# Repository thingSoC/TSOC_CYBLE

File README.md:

# TSOC_CYBLE

A thingSoC Adapter board for the Cypress Semiconductor CYBLE022-001 BLTE Radio Module.

[TSOC_CYBLE](https://github.com/thingSoC/TSOC_CYBLE)

The thingSoC "Grovey Series" was designed as "Everyday Electronics", a no-frills, low cost, approach to modular embedded product design.
thingSoC boards are similar in size to most break-out-boards (BOBs), but feature a standardized stacking pinout, as well as an I2C metadata store (EEPROM)
to indicate what peripherals are installed.

---------------------------------------

## TSOC_CYBLE Application Pictures

[*TSOC_CYBLE*](https://github.com/thingSoC/TSOC_CYBLE)

---------------------------------------

## TSOC_CYBLE Arduino Sketch Examples

Under the "examples" directory are several Arduino IDE examples for using the TSOC_CYBLE board with Arduino IDE.
Using the Arduino "Wire" library for I2C communications, it is simple to control the TSOC_CYBLE

```c

 coming soon...

```

---------------------------------------
## TSOC_CYBLE Programming

You can reprogram the board using any USB to UART adapter :

In order to reprogram the Cypress PSoC4 device, you will need to download and install the PSoC Creator tool, which includes a serial bootloader host application.

Select Tools -> Bootloader Host 

Then select the hex (cyacd) file that you wish to program, and the COM: port of your device. Proess the "Upload" button to reflash the device.

[PSoC Creator Bootloader Host](https://github.com/thingSoC/TSOC_CYBLE)

---------------------------------------
## Other Applications

The TSOC_CYBLE can also drive other devices, such as Servos, Motors, Relays and more.

---------------------------------------

## TSOC_CYBLE Status <a name="TSOC_CYBLE_status"/>

**09/02/2016:** 
Revision 1.0 - Initial Layout 

---------------------------------------
## TSOC_CYBLE Model Images

[TSOC_CYBLE](https://github.com/thingSoC/TSOC_CYBLE)

[TSOC_CYBLE](https://github.com/thingSoC/TSOC_CYBLE)

---------------------------------------

## TSOC_CYBLE Documentation Index <a name="TSOC_CYBLE_documentation_index"/>

[Quick Start Guide](https://github.com/thingSoC/TSOC_CYBLE/blob/master/TSOC_CYBLE/docs/QuickStart.md)

[User Guide](https://github.com/thingSoC/TSOC_CYBLE/blob/master/TSOC_CYBLE/docs/UserGuide.md)

[Theory of Operation](https://github.com/thingSoC/TSOC_CYBLE/blob/master/TSOC_CYBLE/docs/TheoryOfOperation.md)

[thingSoC Organization Website](http://thingSoC.github.io)

[thingSoC FAQ - Frequently Asked Questions](http://thingsoc.github.io/support/faq.html)

---------------------------------------

[ 
*thingSoC*](http://thingsoc.github.io)

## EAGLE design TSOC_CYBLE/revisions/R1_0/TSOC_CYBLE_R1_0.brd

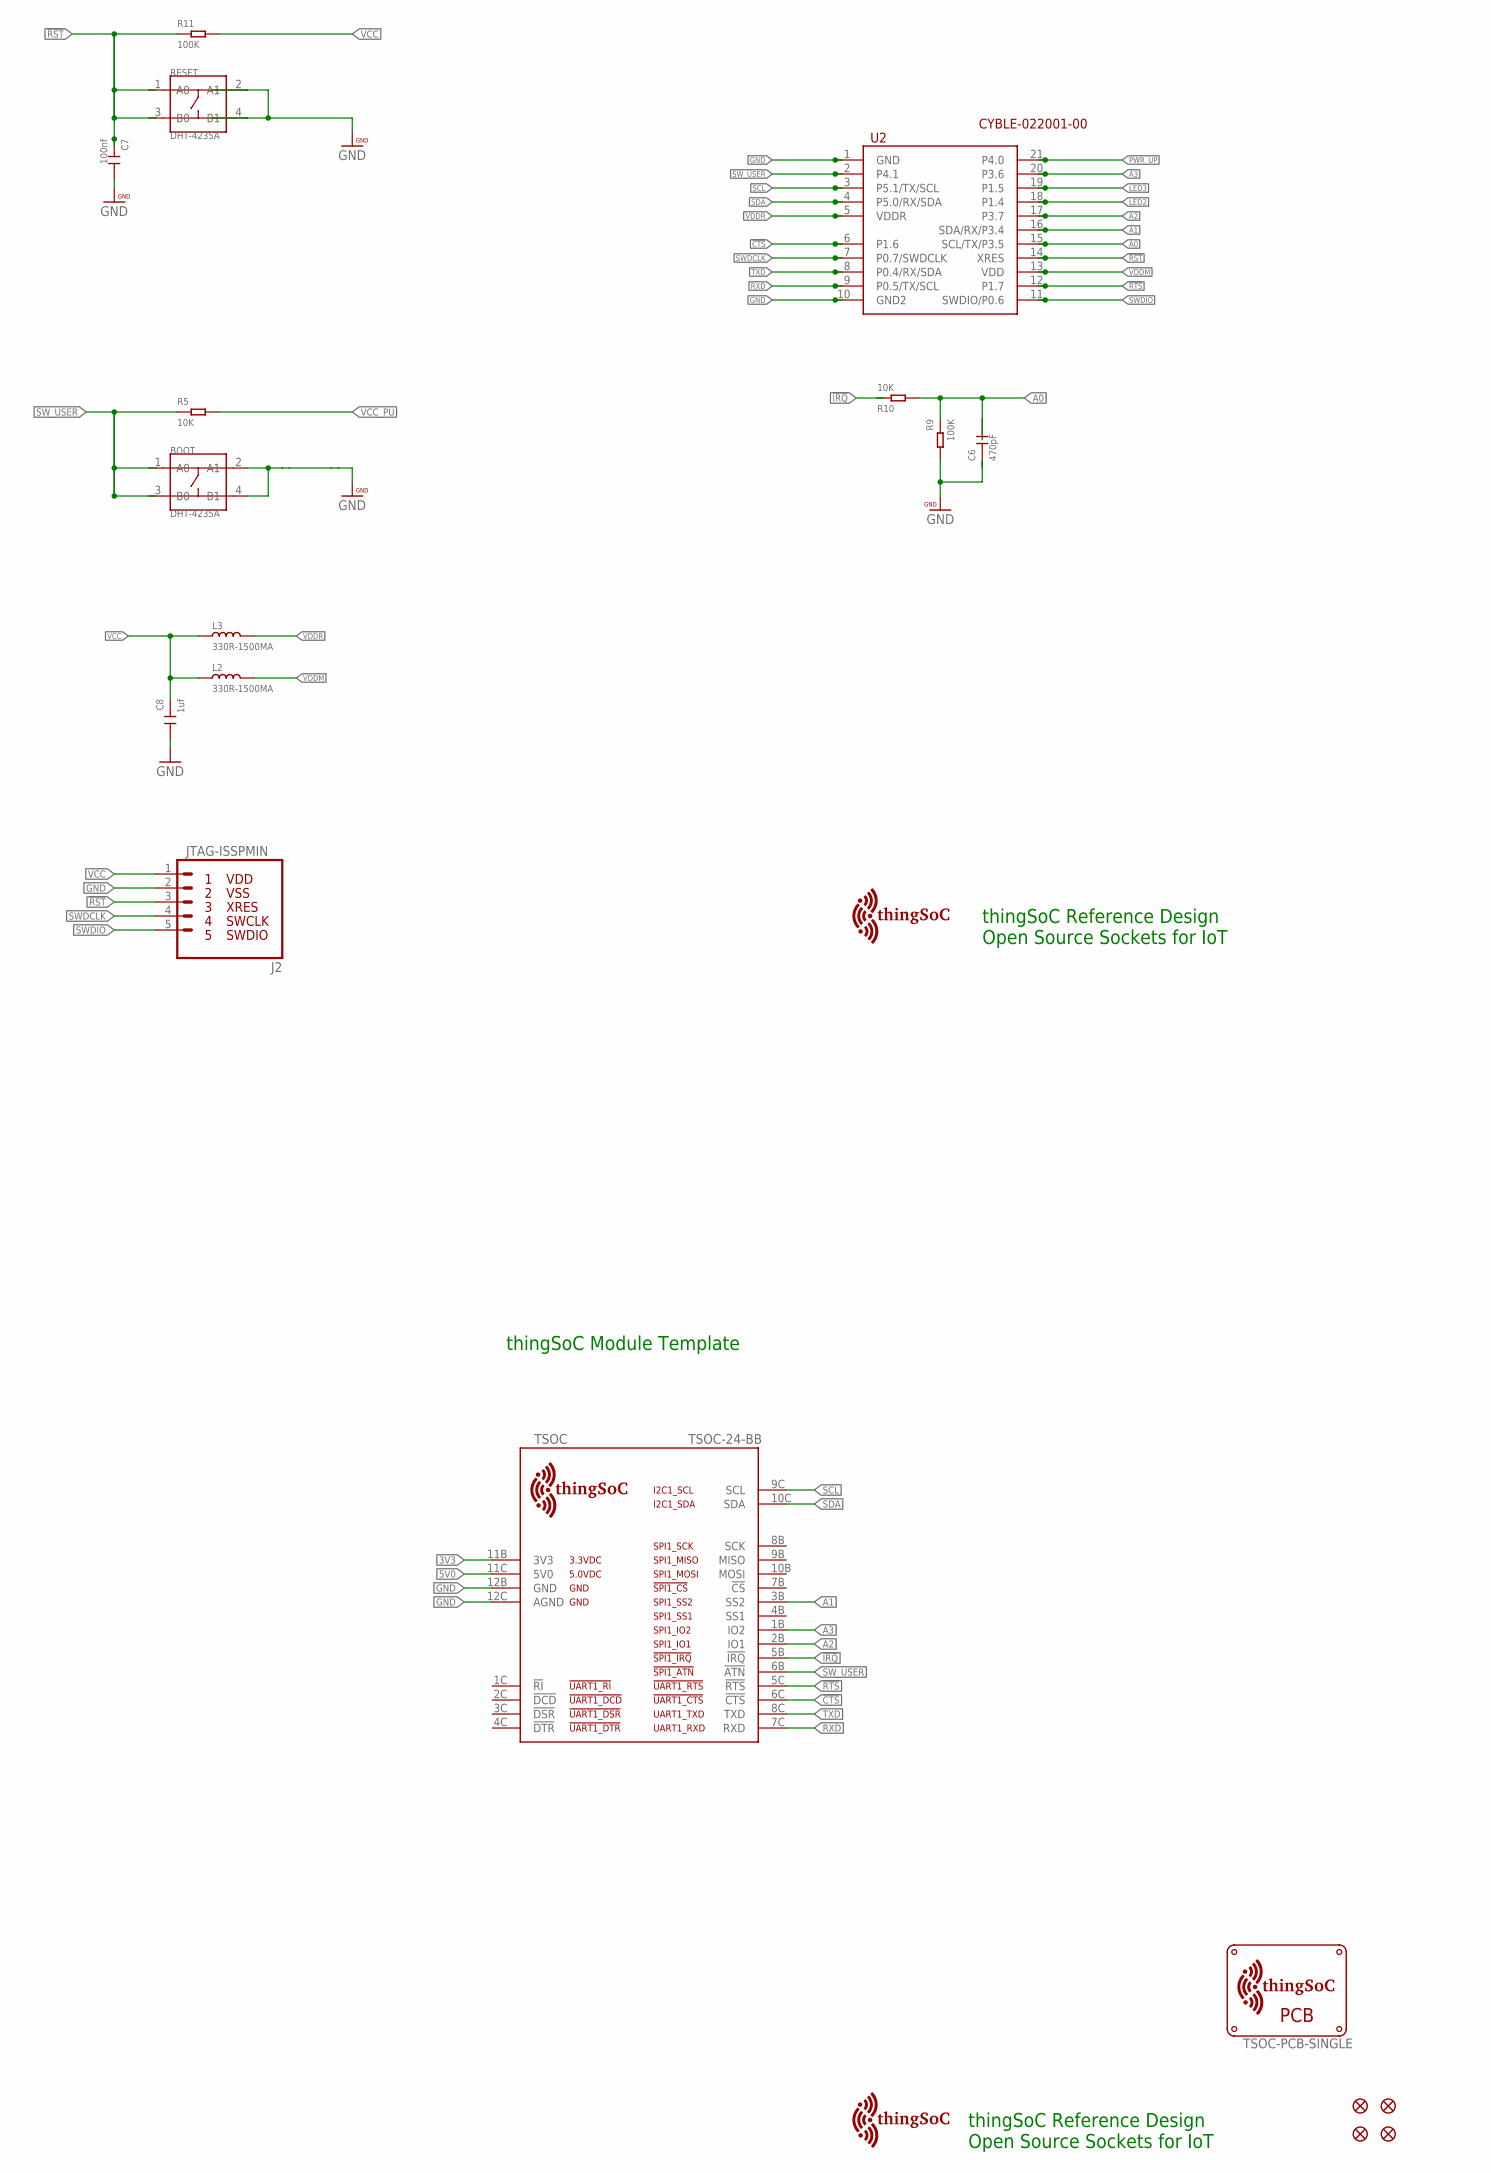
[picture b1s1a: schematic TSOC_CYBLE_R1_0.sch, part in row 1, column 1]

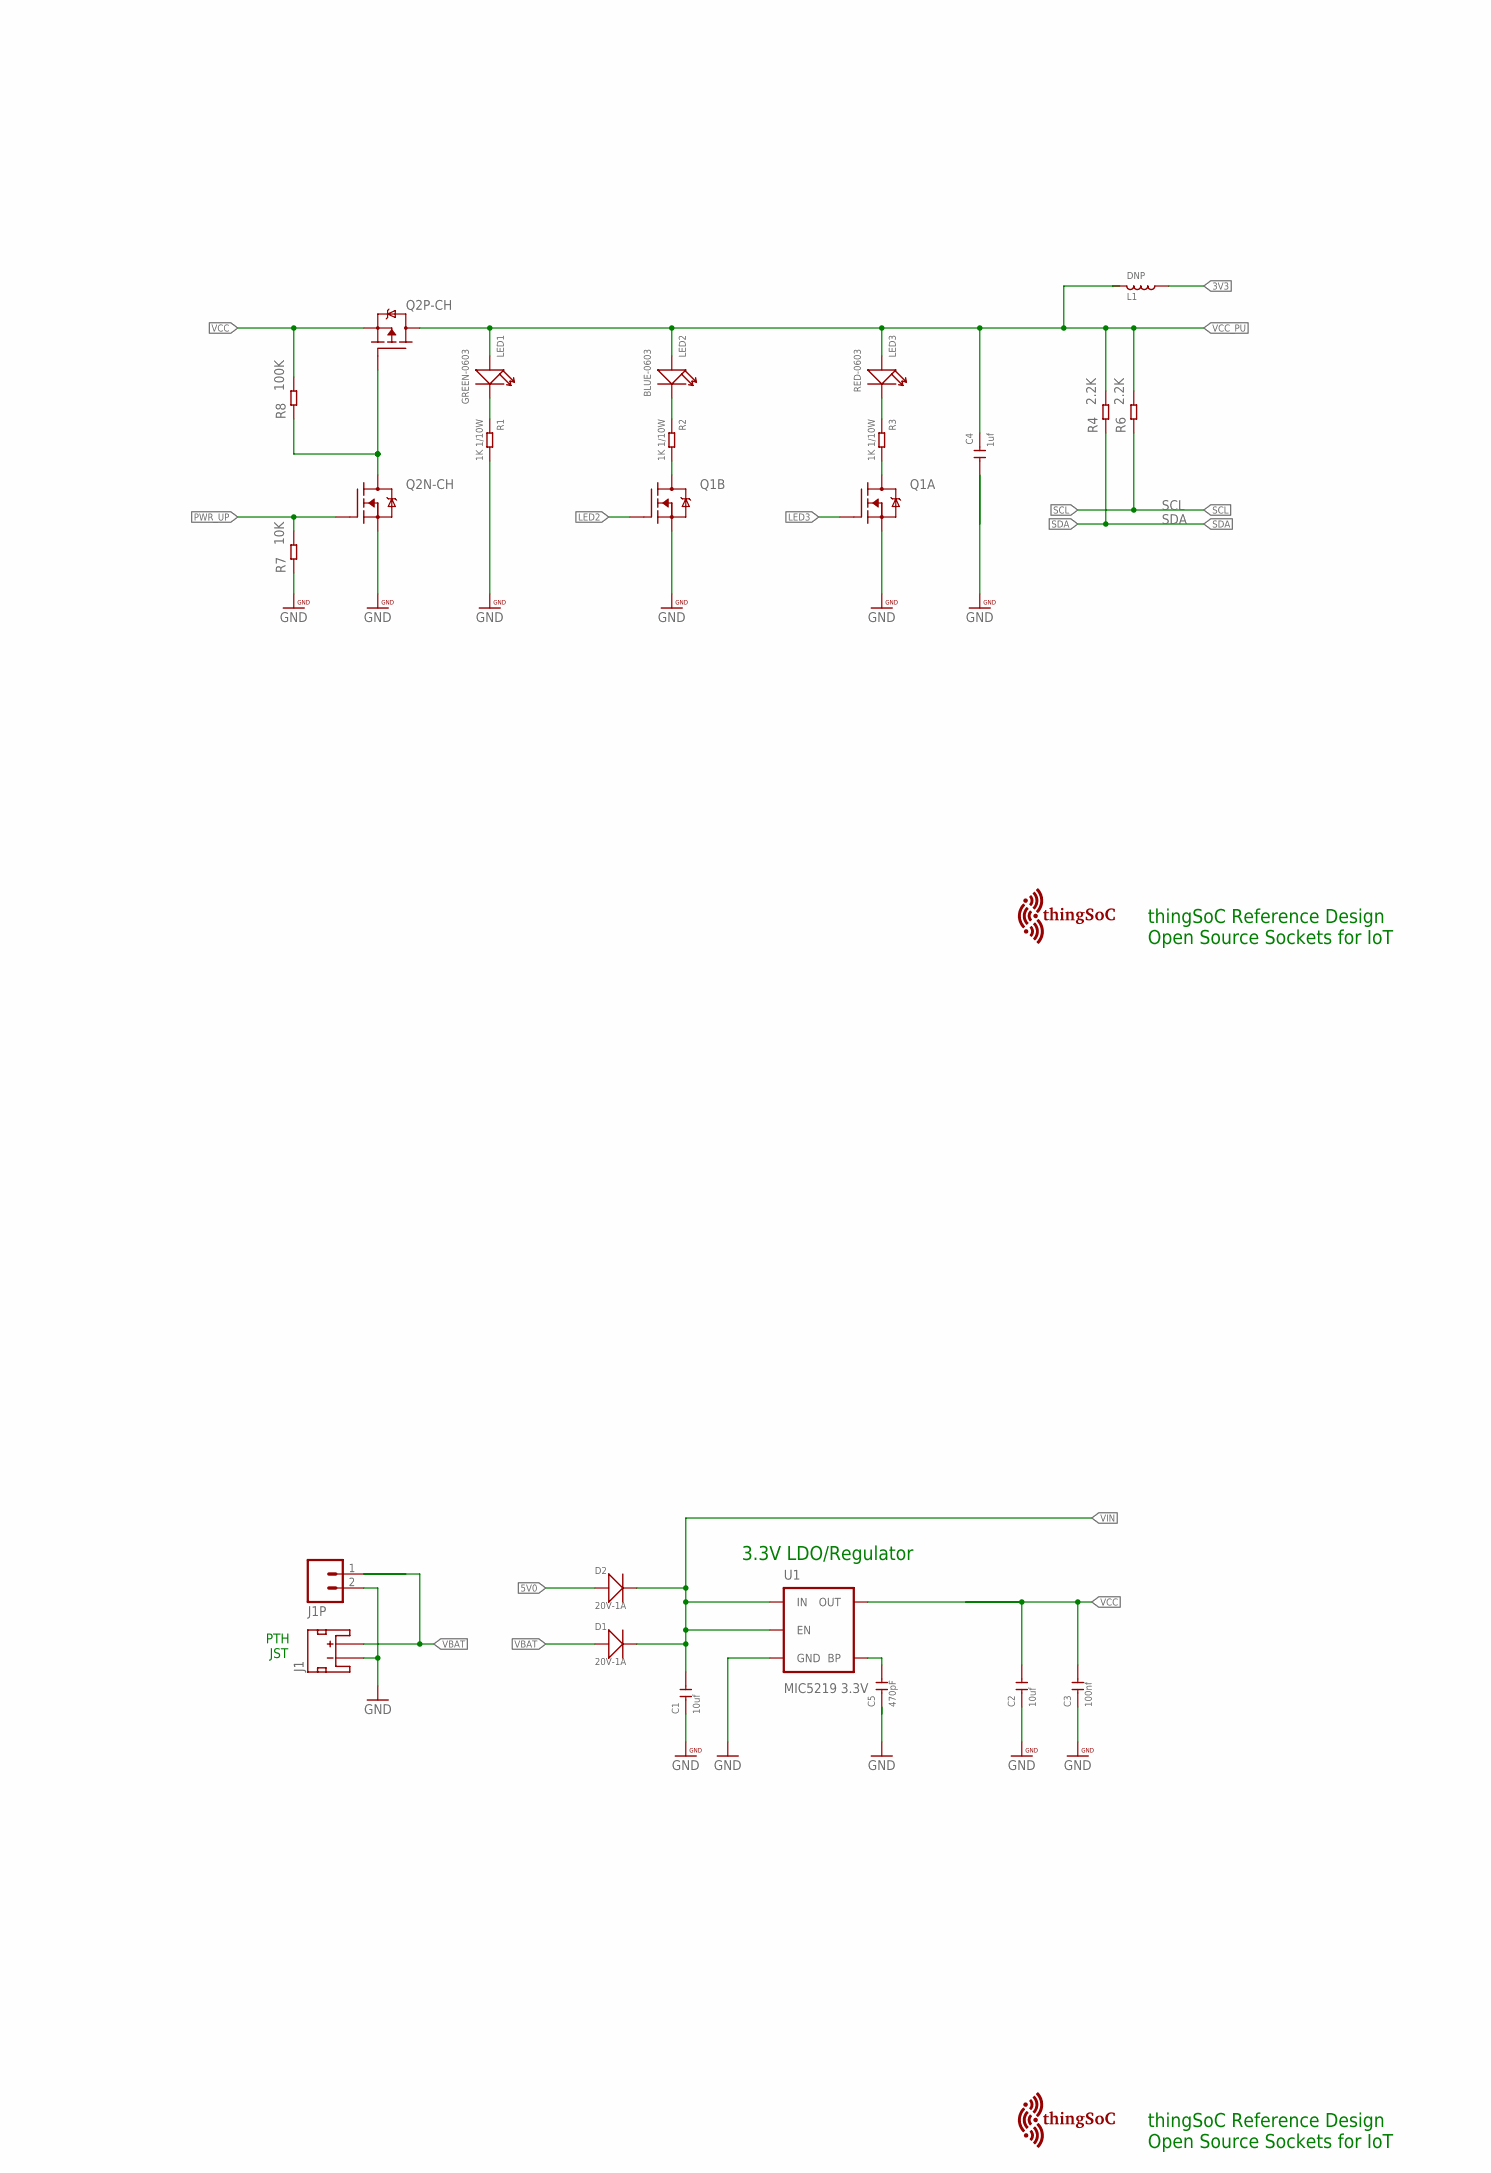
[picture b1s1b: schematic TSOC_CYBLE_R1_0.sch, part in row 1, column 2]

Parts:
$$U$1, $$U$2: TSOC-LOGO-MED
BOOT: DHT-4235A; SW4-SMD-4.2X3.2X2.5MM
C1, C2: 10uf; C1206
C3, C7: 100nf; C0603
C4, C8: 1uf; C0603
C5, C6: 470pF; C0603
D1, D2: 20V-1A; SOD-123
FID1, FID2, FID3, FID4: FIDUCIALUFIDUCIAL; MICRO-FIDUCIAL
J1: JST_2MM_MALE; JST-2-SMD
J1P: M02-JST-2-PTH-NO_SILK; JST-2-PTH-NS
J2: JTAG-ISSPMIN; PSOC_JTAG_MINSILK
L1: DNP; L0603
L2, L3: 330R-1500MA; L0805
LED1: GREEN-0603; LED-0603
LED2: BLUE-0603; LED-0603
LED3: RED-0603; LED-0603
PCB: TSOC-PCB-SINGLE; TSOC-BB-BRD-DIM
Q1: FDG1024NZ; SOT95P280X110-6N
Q2: FDC6420C; SOT95P280X110-6N
R1, R2, R3: 1K 1/10W; R0603
R4, R6: 2.2K; R0603
R5, R7, R10: 10K; R0603
R8, R9, R11: 100K; R0603
RESET: DHT-4235A; SW4-SMD-4.2X3.2X2.5MM
TSOC: TSOC-24-BB; TSOC-BB-S24
U1: MIC5219 3.3V; SOT23-5
U2: CYBLE-022001-00; PROC-BLE-10MM-21
U$100, U$101: TSOC-LOGO-MED

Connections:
3V3: L1.2, TSOC.11B (3V3)
5V0: D2.+, TSOC.11C (5V0)
!CTS: TSOC.6C (!CTS), U2.6 (P1.6)
!IRQ: R10.1, TSOC.5B (!IRQ)
!RST: C7.1, J2.3, R11.1, RESET.1 (A0), RESET.3 (B0), U2.14 (XRES)
!RTS: TSOC.5C (!RTS), U2.12 (P1.7)
A0: C6.2, R9.1, R10.2, U2.15 (SCL/TX/P3.5)
A1: TSOC.3B (SS2), U2.16 (SDA/RX/P3.4)
A2: TSOC.2B (IO1), U2.17 (P3.7)
A3: TSOC.1B (IO2), U2.20 (P3.6)
BYPASS1: C5.2, U1.4 (BP)
GATE: Q2.3 (G), Q2.6 (D), R8.1
GND: BOOT.2 (A1), BOOT.4 (B1), C1.1, C2.1, C3.1, C4.2, C5.1, C6.1, C7.2, C8.2, J1.1 (-), J1P.2, J2.2, Q1.1 (S), Q1.4 (S), Q2.5 (S), R1.2, R7.1, R9.2, RESET.2 (A1), RESET.4 (B1), TSOC.12B (GND), TSOC.12C (AGND), U1.2 (GND), U2.1 (GND), U2.10 (GND2)
L2: Q1.3 (D), R2.2
L3: Q1.6 (D), R3.2
LD1: LED1.-, R1.1
LD2: LED2.-, R2.1
LD3: LED3.-, R3.1
LED2: Q1.5 (G), U2.18 (P1.4)
LED3: Q1.2 (G), U2.19 (P1.5)
PWR_UP: Q2.1 (G), R7.2, U2.21 (P4.0)
RXD: TSOC.7C (RXD), U2.9 (P0.5/TX/SCL)
SCL: R6.1, TSOC.9C (SCL), U2.3 (P5.1/TX/SCL)
SDA: R4.1, TSOC.10C (SDA), U2.4 (P5.0/RX/SDA)
SWDCLK: J2.4, U2.7 (P0.7/SWDCLK)
SWDIO: J2.5, U2.11 (SWDIO/P0.6)
SW_USER: BOOT.1 (A0), BOOT.3 (B0), R5.1, TSOC.6B (!ATN), U2.2 (P4.1)
TXD: TSOC.8C (TXD), U2.8 (P0.4/RX/SDA)
VBAT: D1.+, J1.2 (+), J1P.1
VCC: C2.2, C3.2, C8.1, J2.1, L2.1, L3.1, Q2.2 (S), R8.2, R11.2, U1.5 (OUT)
VCC_PU: C4.1, L1.1, LED1.+, LED2.+, LED3.+, Q2.4 (D), R4.2, R5.2, R6.2
VDDM: L2.2, U2.13 (VDD)
VDDR: L3.2, U2.5 (VDDR)
VIN: C1.2, D1.-, D2.-, U1.1 (IN), U1.3 (EN)

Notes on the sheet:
thingSoC Reference Design Open Source Sockets for IoT
thingSoC Module Template
PTH JST
3.3V LDO/Regulator

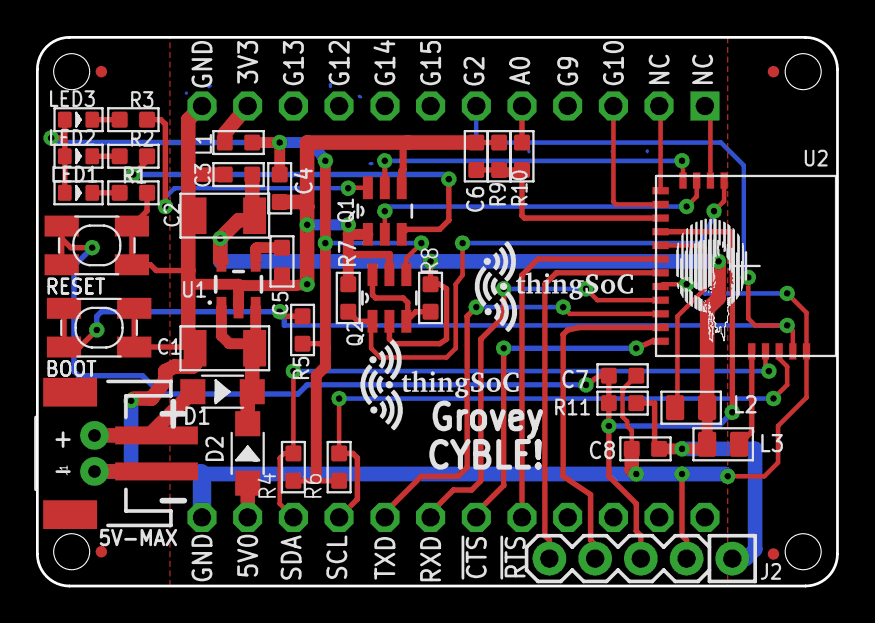
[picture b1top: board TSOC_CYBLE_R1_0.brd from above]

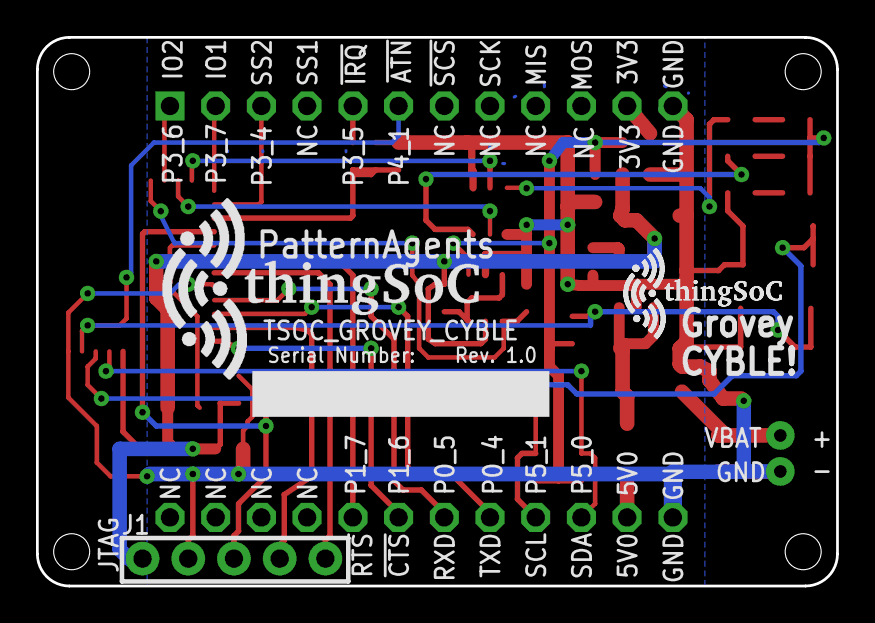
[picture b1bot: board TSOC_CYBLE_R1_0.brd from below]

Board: 2 copper layers, 44.5 x 30.5 mm, 47 parts (4 on the bottom side), 34 nets.

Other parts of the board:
U$102: TSOC-LOGO-LRG

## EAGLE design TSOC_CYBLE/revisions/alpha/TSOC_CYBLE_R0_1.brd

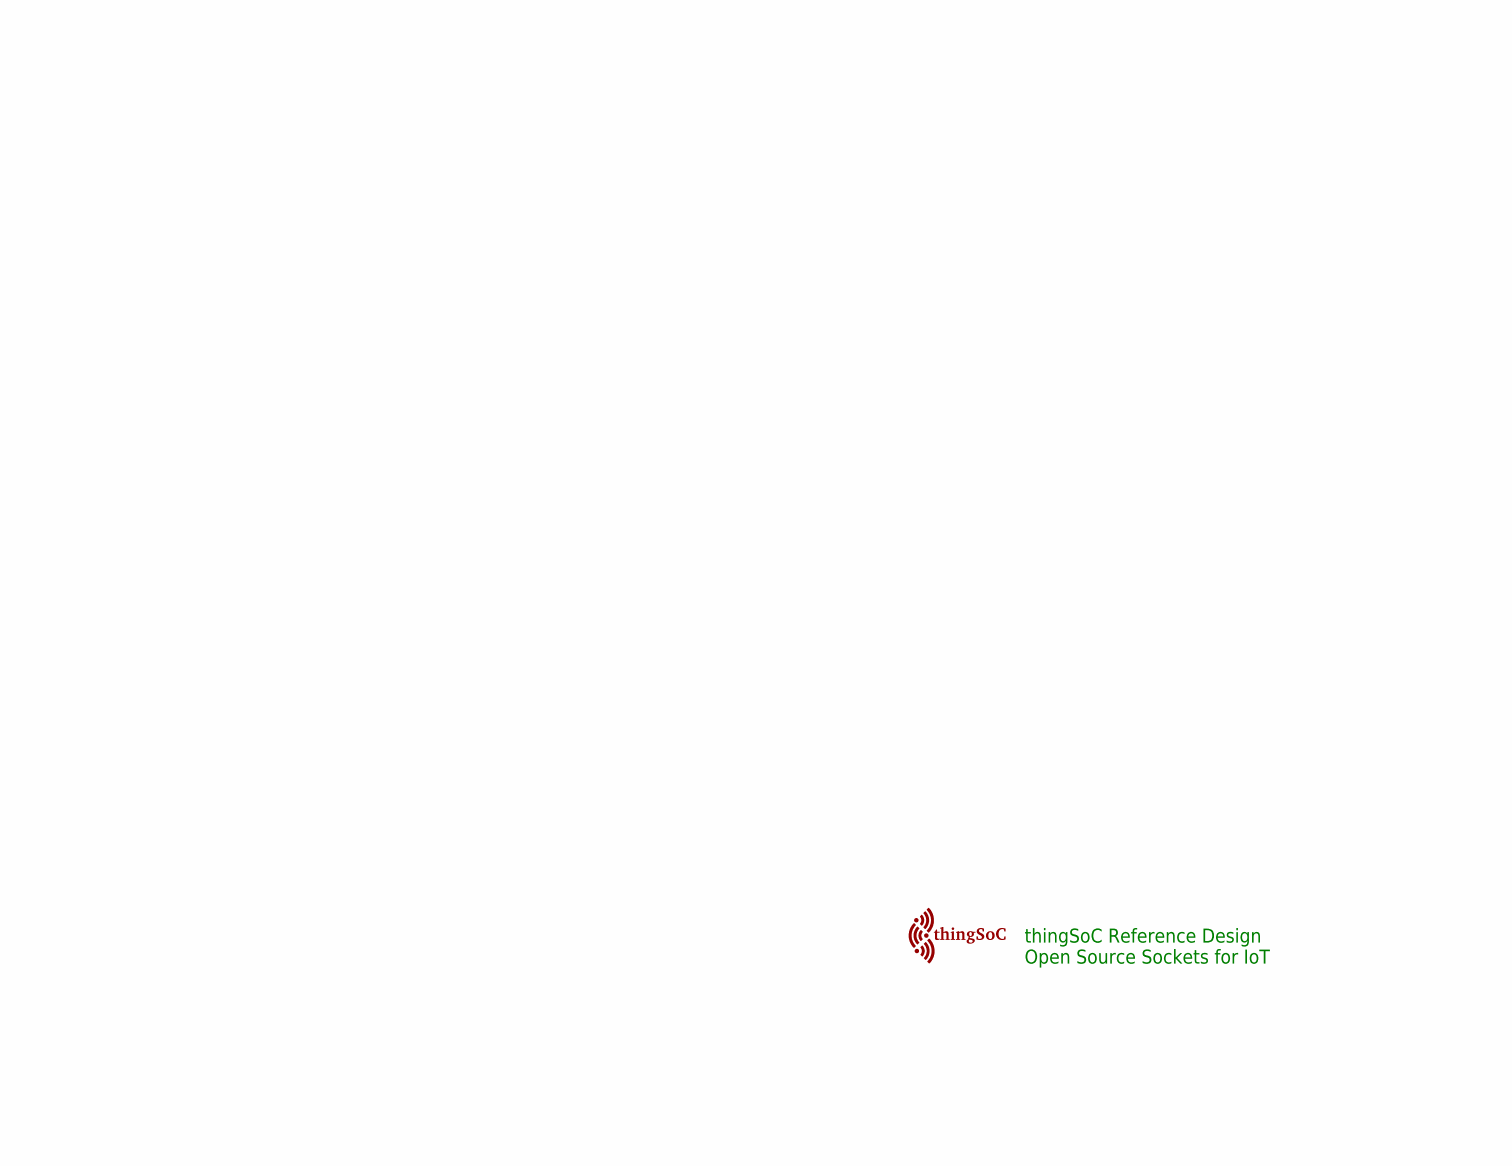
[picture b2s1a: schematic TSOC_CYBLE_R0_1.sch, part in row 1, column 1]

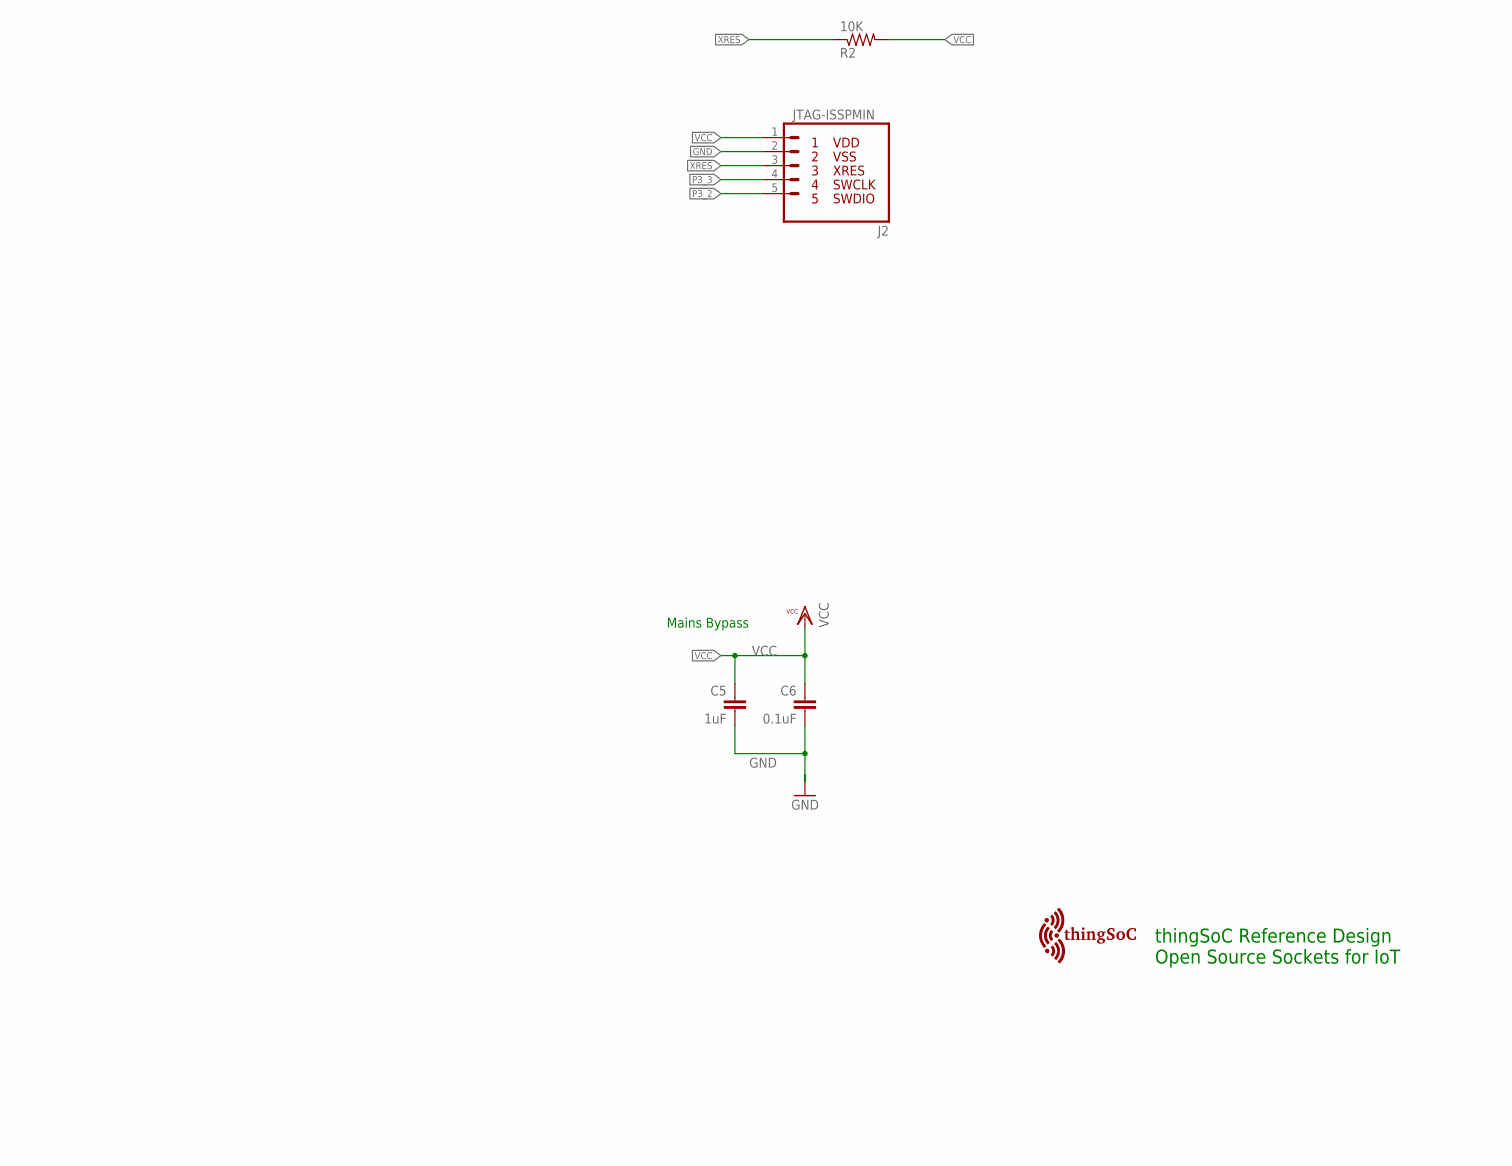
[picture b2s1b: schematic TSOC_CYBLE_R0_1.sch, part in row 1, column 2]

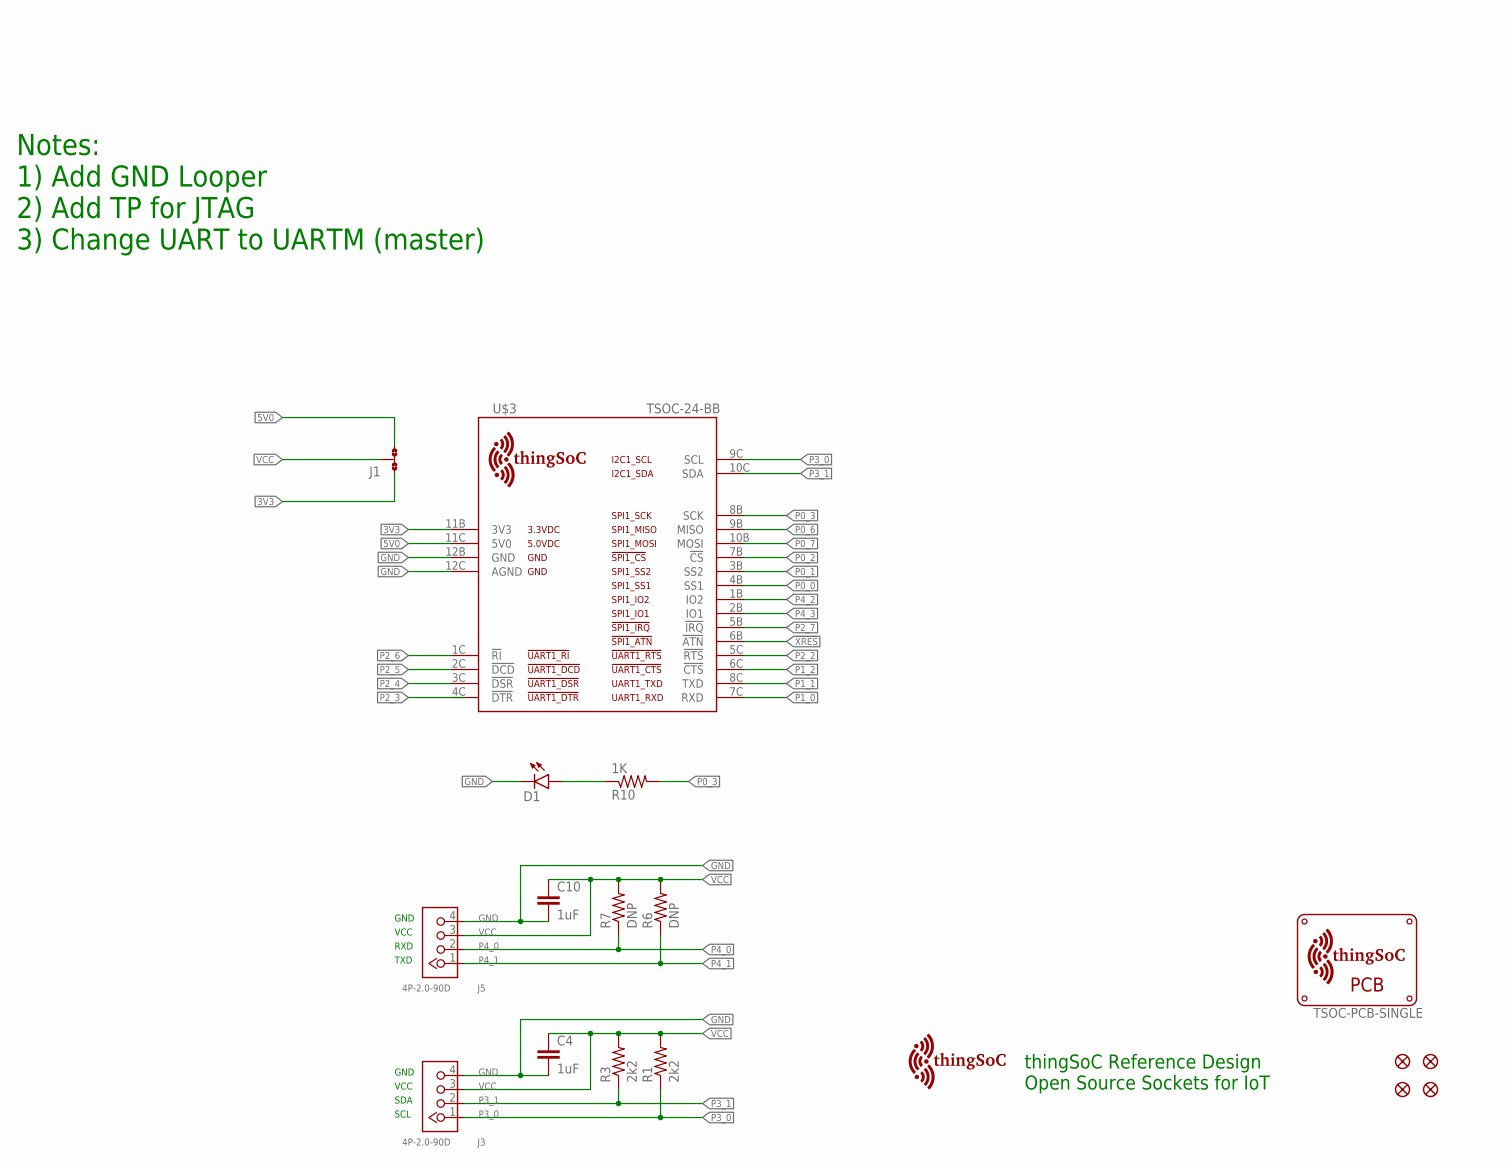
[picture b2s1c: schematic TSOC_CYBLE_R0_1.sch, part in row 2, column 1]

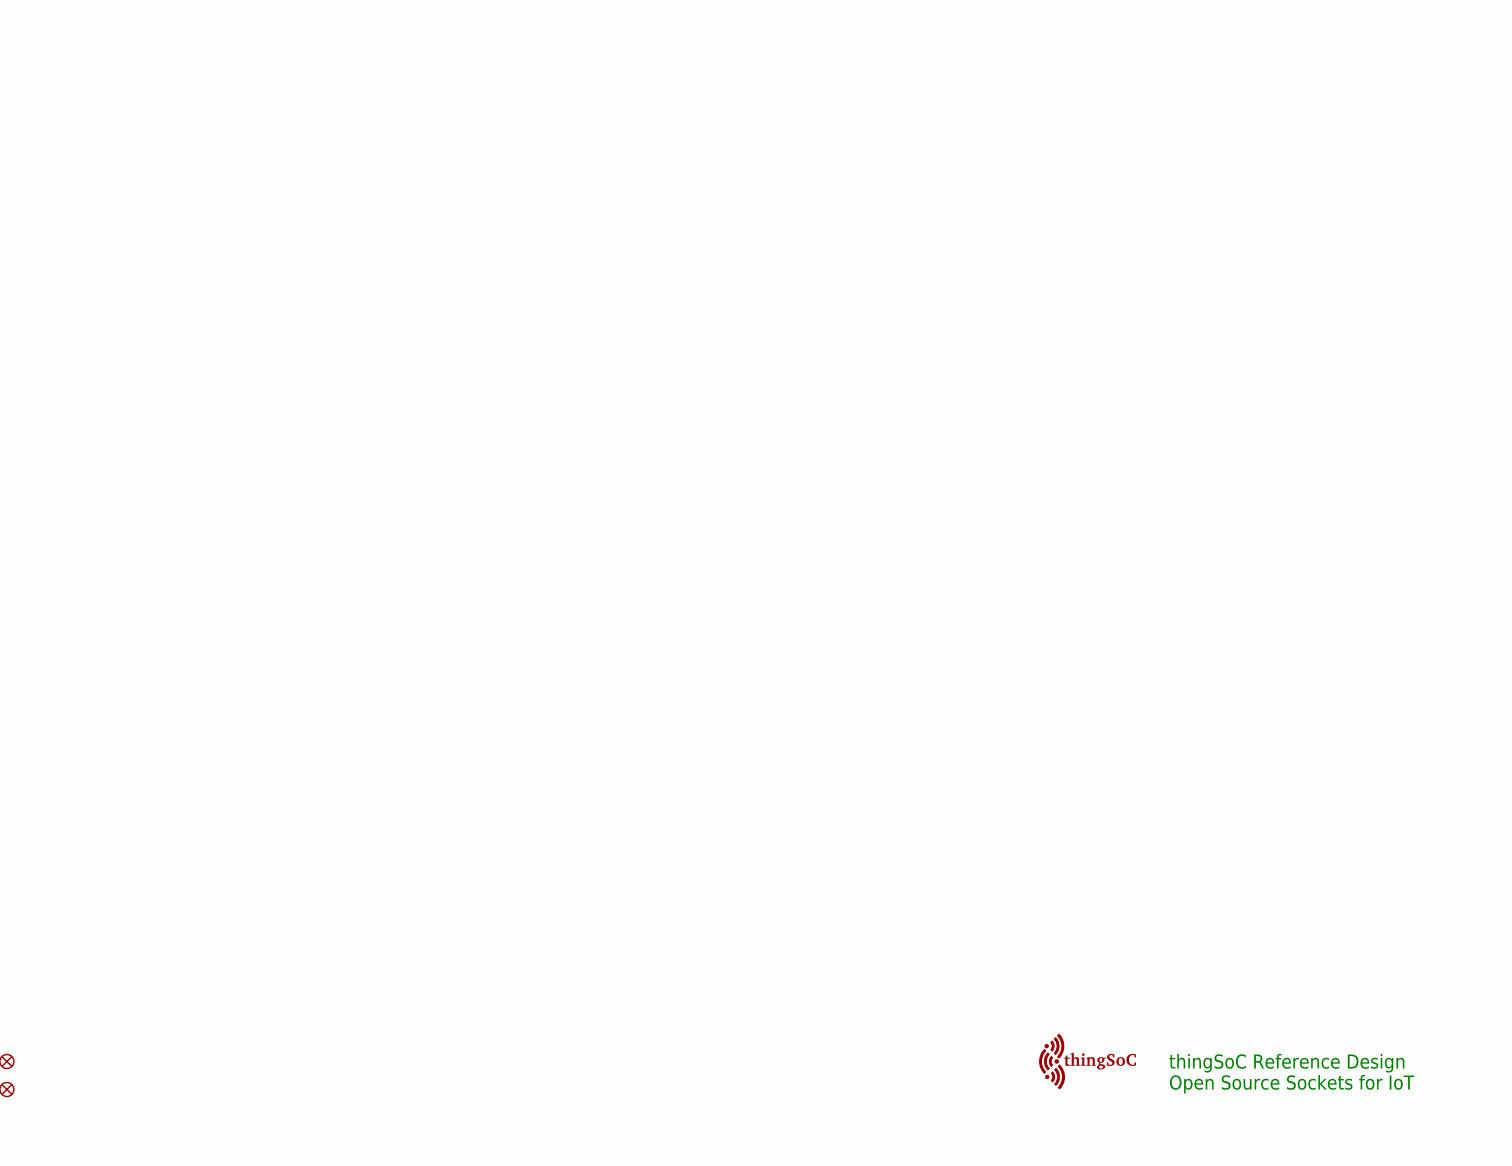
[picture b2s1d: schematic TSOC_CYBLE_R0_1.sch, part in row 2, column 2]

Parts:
C4, C5, C10: 1uF; 0603-CAP
C6: 0.1uF; 0603-CAP
D1: LED0603; LED-0603
FID1, FID2, FID3, FID4: FIDUCIALUFIDUCIAL; MICRO-FIDUCIAL
J1: JMP-3-NO-PTH; JMP-3-NO-PTH-2.54
J2: JTAG-ISSPMIN; PSOC_JTAG_MINSILK
J3, J5: 4P-2.0-90D; HW4-2.0-90D
R1, R3: 2k2; 0603-RES
R2: 10K; 0603-RES
R6, R7: DNP; 0603-RES
R10: 1K; 0603-RES
U$1, U$4: TSOC-LOGO-MED
U$2: TSOC-PCB-SINGLE; TSOC-BB-BRD-DIM
U$3: TSOC-24-BB; TSOC-BB-S24
U$100: TSOC-LOGO-SMALL; TSOC-LOGO-SML
U$101: TSOC-LOGO-LRG

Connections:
3V3: J1.1, U$3.11B (3V3)
5V0: J1.3, U$3.11C (5V0)
!XRES: J2.3, R2.1, U$3.6B (!ATN)
GND: C4.2, C5.2, C6.2, C10.2, D1.C, J2.2, J3.4, J5.4, U$3.12B (GND), U$3.12C (AGND)
unnamed: D1.A, R10.1
P0_0: U$3.4B (SS1)
P0_1: U$3.3B (SS2)
P0_2: U$3.7B (!CS)
P0_3: R10.2, U$3.8B (SCK)
P0_6: U$3.9B (MISO)
P0_7: U$3.10B (MOSI)
P1_0: U$3.7C (RXD)
P1_1: U$3.8C (TXD)
P1_2: U$3.6C (!CTS)
P2_2: U$3.5C (!RTS)
P2_3: U$3.4C (!DTR)
P2_4: U$3.3C (!DSR)
P2_5: U$3.2C (!DCD)
P2_6: U$3.1C (!RI)
P2_7: U$3.5B (!IRQ)
P3_0: J3.1, R1.1, U$3.9C (SCL)
P3_1: J3.2, R3.1, U$3.10C (SDA)
P3_2: J2.5
P3_3: J2.4
P4_0: J5.2, R7.1
P4_1: J5.1, R6.1
P4_2: U$3.1B (IO2)
P4_3: U$3.2B (IO1)
VCC: C4.1, C5.1, C6.1, C10.1, J1.2, J2.1, J3.3, J5.3, R1.2, R2.2, R3.2, R6.2, R7.2

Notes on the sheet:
Notes: 1) Add GND Looper 2) Add TP for JTAG 3) Change UART to UARTM (master)
thingSoC Reference Design Open Source Sockets for IoT
Mains Bypass
GND
VCC
TXD
RXD
SDA
SCL

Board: 2 copper layers, 26 parts (3 on the bottom side), 11 nets, no tracks yet.

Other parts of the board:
U$102: TSOC-LOGO-SMALL; TSOC-LOGO-SML

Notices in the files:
parts and their libraries:
thingSoC: License : http://creativecommons.org/licenses/by-sa/4.0
(Creative Commons 4.0)
PatternAgents-Fairchild: (Creative Commons 3.0)
PatternAgents-Cypress: License : http://creativecommons.org/licenses/by-sa/3.0
